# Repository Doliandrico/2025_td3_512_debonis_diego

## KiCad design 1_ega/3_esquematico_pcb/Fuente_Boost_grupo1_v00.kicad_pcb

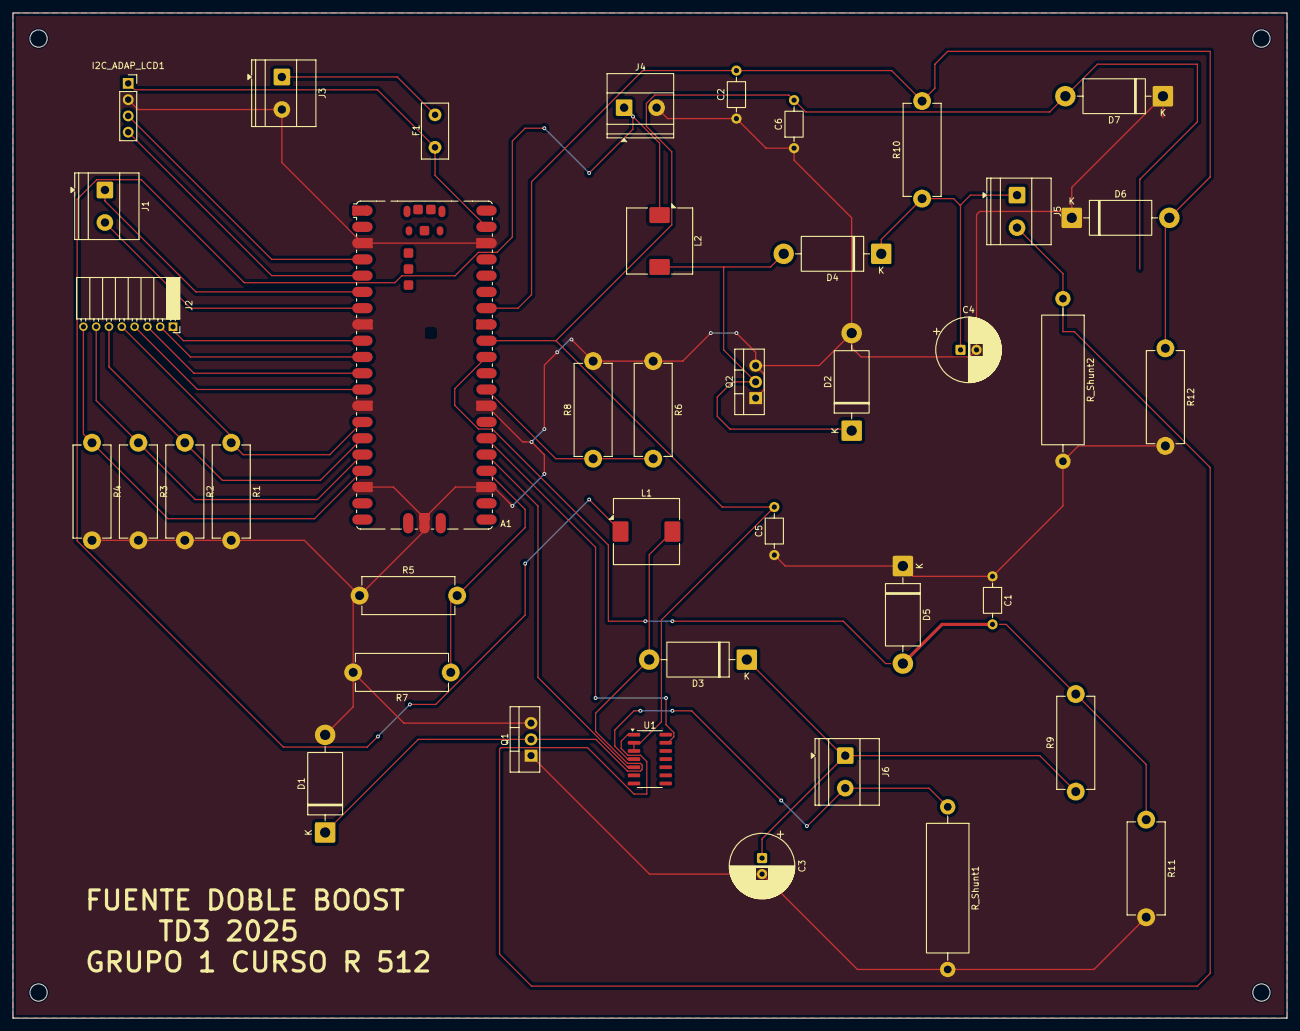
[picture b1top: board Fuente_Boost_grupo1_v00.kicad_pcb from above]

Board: 2 copper layers, 199.0 x 157.0 mm, 41 parts (0 on the bottom side), 29 nets.

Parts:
A1: RaspberryPi_Pico; RaspberryPi_Pico_SMD
C1, C2, C5, C6: C_Small; C_Axial_L3.8mm_D2.6mm_P7.50mm_Horizontal
C3, C4: C_Polarized; CP_Radial_D10.0mm_P2.50mm
D1, D2, D5, D6, D7: UF5408; D_DO-201AD_P15.24mm_Horizontal
D3, D4: 1N5822; D_DO-201AD_P15.24mm_Horizontal
F1: Fuse_Small; Fuse_Littelfuse_395Series
I2C_ADAP_LCD1: Conn_01x04; PinSocket_1x04_P2.54mm_Vertical
J1: EGB; TerminalBlock_Phoenix_MKDS-1,5-2-5.08_1x02_P5.08mm_Horizont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
J2: Conn_01x08; PinSocket_1x08_P2.00mm_Horizontal
J3: Fuente_Alimentación_Placa_5Vcc; TerminalBlock_Phoenix_MKDS-1,5-2-5.08_1x02_P5.08mm_Horizont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
J4: Fuente_laboratorio_5Vcc; TerminalBlock_Phoenix_MKDS-1,5-2-5.08_1x02_P5.08mm_Horizont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
J5, J6: OUT1; TerminalBlock_Phoenix_MKDS-1,5-2-5.08_1x02_P5.08mm_Horizont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
L1, L2: L; L_TDK_SLF10165
Q1, Q2: IRF540N; TO-220-3_Vertical
R1, R2, R3, R4, R5, R6, R7, R8, R9, R10, R11, R12: R; R_Axial_DIN0614_L14.3mm_D5.7mm_P15.24mm_Horizontal
R_Shunt1, R_Shunt2: R_Small; R_Axial_Power_L20.0mm_W6.4mm_P25.40mm
U1: CD4066BM; SO-14_3.9x8.65mm_P1.27mm

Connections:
/VShunt1: J6.2, R_Shunt1.1, U1.4
/VShunt2: J5.2, R_Shunt2.1, U1.1
/Vout1: C3.1, D3.1 (K), J6.1, R9.1
/Vout2: C4.1, D4.1 (K), J5.1, R10.1
ADC0: A1.31 (GPIO26_ADC0), R9.2, R11.1
ADC1: A1.32 (GPIO27_ADC1), C5.2, C6.2, D7.2 (A), U1.2, U1.3
ADC2: A1.34 (GPIO28_ADC2), C2.2, D6.2 (A), R10.2, R12.1
GND: A1.3 (GND), A1.8 (GND), A1.13 (GND), A1.18 (GND), A1.23 (GND), A1.28 (GND), A1.38 (GND), A1.D2 (GND), C1.1, C2.1, C3.2, C4.2, C5.1, C6.1, D1.2 (A), D2.2 (A), D5.1 (K), D6.1 (K), D7.1 (K), I2C_ADAP_LCD1.2, J3.2, J4.2, Q1.1 (G), Q1.3 (S), Q2.1 (G), Q2.3 (S), R1.2, R2.2, R3.2, R4.2, R5.1, R6.1, R7.2, R8.2, R11.2, R12.2, R_Shunt1.2, R_Shunt2.2
GP19: A1.25 (GPIO19), U1.5
GP20: A1.26 (GPIO20), U1.13
I2C1-SDA: A1.4 (GPIO2), I2C_ADAP_LCD1.3
I2C1-SDL: A1.5 (GPIO3), I2C_ADAP_LCD1.4
unnamed: D1.1 (K), D3.2 (A), L1.2, Q1.2 (D)
unnamed: D2.1 (K), D4.2 (A), L2.2, Q2.2 (D)
unnamed: F1.2, J3.1
PWM_1A: A1.24 (GPIO18), R5.2, R7.1
PWM_3A: A1.29 (GPIO22), R6.2, R8.1
TECLADO_COLUMNA_1: A1.17 (GPIO13), J2.8, R4.1
TECLADO_COLUMNA_2: A1.16 (GPIO12), J2.7, R3.1
TECLADO_COLUMNA_3: A1.15 (GPIO11), J2.6, R2.1
TECLADO_COLUMNA_4: A1.14 (GPIO10), J2.5, R1.1
TECLADO_FILA_1: A1.9 (GPIO6), J2.1
TECLADO_FILA_2: A1.10 (GPIO7), J2.2
TECLADO_FILA_3: A1.11 (GPIO8), J2.3
TECLADO_FILA_4: A1.12 (GPIO9), J2.4
UART1-RX: A1.7 (GPIO5), J1.2
UART1-TX: A1.6 (GPIO4), J1.1
VSYS_Vin: A1.39 (VSYS), F1.1, I2C_ADAP_LCD1.1
Vin: J4.1, L1.1, L2.1

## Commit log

2025-06-09 Primera consigna de TP2
2025-06-09 Segunda consigna de TP2
2025-06-18 Primera consigna de TP3
2025-06-18 Segunda consigna de TP3
2025-07-02 Primera entrega EGAv1
2025-07-06 Primera consigna de TP4
2025-07-09 Segunda consigna de TP4
2025-07-09 Imagenes de diagramas en bloques EGA/v1
2025-07-09 Guia de codigo de la segunda consigna de TP4
2025-07-17 Entrega EGA/v2
2025-07-17 Cambio Diagrama de tareas.jpg a .png
